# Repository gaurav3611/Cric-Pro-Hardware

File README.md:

# SSwinGG bat sensor: hardware and firmware, step by step

A small sensor that sits on a cricket bat and sends every movement of the bat to the SSwinGG dashboard over Bluetooth. This folder holds the circuit, the firmware, and a guide that builds it one stage at a time, so that each stage is tested before the next part is added.

It is written for someone who has not done this before. Each stage says what to wire, what to upload, what you should see, and what is going on between the parts.

## What has been checked, and what has not

- **Checked:** every sketch compiles for the ESP32-C3 Super Mini, with no warnings. Stages 1 to 8 have also been run on a computer against a pretend sensor, battery and dashboard, and what they print, send and do with the light was checked there. The 14-byte Bluetooth packet was read back with the web app's own code.
- **Not checked:** nothing here has run on real hardware yet. The pin orders in the drawings come from published pinouts, not from your boards, the battery circuit has not been built, and the printed circuit board has not been made.

So follow the stages in order, and trust the labels printed on your own boards over any drawing.

## Versions

**0.2.0, 2026-10-21.** C2, a 220 µF capacitor that steadies the 5V line, added to both zero PCB layouts and the full circuit. A proposed impact sensor: [a piezo disc wired without diodes](diagrams/impact-piezo.svg), not yet read by the firmware. The continuity tester also runs on an ESP32 DevKit. The phone app moved to [mobile_app_swing](https://github.com/gaurav3611/mobile_app_swing).

**0.1.0, 2026-10-17.** First version: the circuit, nine stages, the guides as PDF, the one-file firmware and the layout without the diode.

## Parts

| Part | Notes |
|---|---|
| ESP32-C3 Super Mini | The small board with a USB-C socket and eight pins on each side. |
| GY-BMI160 | The motion sensor board: acceleration and rotation on three axes each. |
| LiPo cell, 3.7 V, 1500 mAh | One cell with two leads. Buy one with a built-in protection board, which is the usual kind. |
| TP4056 charger module **with protection** | The version with six pads: `IN+ IN- B+ B- OUT+ OUT-`. See [the question about the charger](#is-the-tp4056-the-right-charger). |
| Slide switch | Three pins in a row, 2.54 mm apart, for example the SS12D00. |
| Diode 1N5817 | A Schottky diode. A 1N5819 also works and loses a little more voltage. |
| Zero PCB | At least 20 by 16 holes. The common 5 by 7 cm board is big enough. |
| Female header strips | Two with 8 pins, one with 7. With them the two boards can be unplugged. |
| Insulated hook-up wire | Thin single-strand wire. |
| USB-C cable that carries data | Charge-only cables give no serial port. |
| Phone charger, 5 V and 1 A or more | To charge the cell through the TP4056. |
| Only for stage 7 | Two 100 kilohm resistors and one 100 nanofarad ceramic capacitor. |

Tools: a soldering iron and solder, a multimeter, wire cutters, insulating tape or heat-shrink tube, and double-sided foam tape for mounting.

**[docs/parts-to-buy.pdf](docs/parts-to-buy.pdf) is the shopping list:** the exact name to search for, how many, and what to check before paying.

## Before you touch the battery

A LiPo cell stores a lot of energy and can catch fire when it is mistreated.

- **Never let the red and the black lead touch.** Cut and solder them one at a time, never both together.
- **Check which lead is plus with a multimeter** before soldering. Red is normally plus, but plugs are wired both ways.
- **Charge it only through the TP4056**, on a surface that cannot burn, and not unattended.
- **Do not use a cell that is swollen, dented or punctured.**
- **Protect it on the bat.** Mount it away from where the ball hits, with foam under it.

## The stages

Do them in order. Each folder under [stages/](stages/) holds one sketch and a page, `README.pdf`, with the steps. The links in the table open those pages.

| Stage | What you add | What you learn | It works when |
|---|---|---|---|
| [1. Blink](stages/01_blink/README.pdf) | The ESP32 board and a USB cable | Uploading, the Serial Monitor, outputs and inputs | The light blinks and lines appear |
| [2. I2C scan](stages/02_i2c_scan/README.pdf) | The sensor, on five wires | What I2C is, and addresses | It prints `RESULT: PASS` |
| [3. Read the sensor](stages/03_imu_read/README.pdf) | Nothing | Registers, bytes, counts and units | Four checks pass and z reads 1 g |
| [4. Swing speed](stages/04_swing_speed/README.pdf) | Nothing | Calibration, and the speed formula | A swing prints a speed |
| [5. Bluetooth](stages/05_ble_stream/README.pdf) | Nothing | Advertising, connecting, notifications, the packet | The test page shows 50 readings a second |
| [6. Battery](stages/06_battery_power/README.pdf) | Cell, charger, switch, diode | Where the power flows, charging, brownouts | It runs with no cable and counts no brownouts |
| [7. Battery level](stages/07_battery_level/README.pdf) | Optional: two resistors, one capacitor | Measuring a voltage | The printed voltage matches a multimeter |
| [8. The bat firmware](stages/08_sswingg_bat/README.pdf) | Nothing | How it all fits together | The dashboard records a shot |
| [9. WiFi](stages/09_wifi_to_api/README.pdf) | Optional: nothing | WiFi, HTTP and JSON | The API lists the bat as online |

Stages 1 to 5 run from the USB cable. The battery comes in at stage 6, when everything else is known to work.

## The whole circuit

| From | To | What it carries | Added in |
|---|---|---|---|
| `3V3` | `VIN` of the sensor | Power for the sensor, 3.3 volts | Stage 2 |
| `GND` | `GND` of the sensor | Ground | Stage 2 |
| `GPIO4` | `SCL` | I2C clock | Stage 2 |
| `GPIO3` | `SDA` | I2C data | Stage 2 |
| `SAO` of the sensor | `GND` | Fixes the sensor's address at 0x68 | Stage 2 |
| Cell, red lead | `B+` of the charger | Battery plus | Stage 6 |
| Cell, black lead | `B-` of the charger | Battery minus | Stage 6 |
| `OUT+` of the charger | Switch, an end pin | Battery plus, protected | Stage 6 |
| Switch, middle pin | Diode, plain end | Battery plus, switched | Stage 6 |
| Diode, striped end | `5V` | Power into the ESP32 board | Stage 6 |
| `OUT-` of the charger | `GND` | Ground | Stage 6 |
| Switch, middle pin | R1 | Battery plus, switched | Stage 7 |
| `GPIO0` | middle of R1 and R2 | Half the battery voltage. C1 goes from here to ground. | Stage 7 |
| R2, other end | `GND` | Ground | Stage 7 |

Leave the sensor's `3V3`, `CS`, `INT1`, `INT2` and `OCS` pins unconnected.

More drawings:

- [What each pin of the ESP32 is used for](diagrams/pin-map.svg)
- [The sensor on five wires](diagrams/stage-2-sensor-wiring.svg)
- [Where the power flows](diagrams/stage-6-power.svg)
- [Measuring the battery](diagrams/stage-7-battery-sense.svg)
- [Zero PCB layout, hole by hole](diagrams/zero-pcb-layout.svg), with the steps in [docs/build-on-zero-pcb.pdf](docs/build-on-zero-pcb.pdf)
- [The same layout without the diode](diagrams/zero-pcb-layout-no-diode.svg), with a wire in its place
- The printed circuit board, designed in KiCad: [the schematic](diagrams/pcb-schematic.svg), [the parts side](diagrams/pcb-top.svg) and [the solder side](diagrams/pcb-bottom.svg), with ordering and soldering steps in [docs/order-the-pcb.pdf](docs/order-the-pcb.pdf). No board has been made yet.

- [Impact sensor, a proposal](diagrams/impact-piezo.svg): a piezo disc on the blade, wired without diodes. The firmware does not read it yet.

## Is the TP4056 the right charger?

Yes. The chip is called TP4056. There is no common charger called TP4050, so that is almost certainly the module you have.

- **What it does.** It charges one LiPo cell from 5 volts. It holds the current steady until the cell reaches 4.2 volts, then holds 4.2 volts until the current has dropped to a tenth, and then stops.
- **Get the version with protection.** It has six pads instead of four, and two extra small chips. They disconnect the cell when it is drained below about 2.4 volts, charged above about 4.3 volts, or shorted.
- **The charging current is 1 amp as sold.** That suits a 1500 mAh cell: cells are normally charged at up to their capacity per hour, which here is 1.5 amps. A full charge takes about two hours. To charge more gently, see [docs/make-changes.pdf](docs/make-changes.pdf).
- **The ESP32-C3 Super Mini has no charger of its own**, which is why this module is needed.
- **It is not a switch and not a regulator.** The slide switch turns the bat off. The regulator on the ESP32 board makes the 3.3 volts.

## Set up the Arduino IDE

1. **Install the Arduino IDE**, version 2, from arduino.cc.
2. **Add the ESP32 boards:** Tools > Board > Boards Manager, search for `esp32`, and install "esp32 by Espressif Systems". This kit was compiled with version 3.3.11.
3. **Choose the board:** Tools > Board > esp32 > **Nologo ESP32C3 Super Mini**.
4. **Choose the port:** Tools > Port, the one that appears when the board is plugged in. On a Mac its name starts with `/dev/cu.usbmodem`.
5. **Open a sketch** with File > Open and pick the `.ino` file inside a stage folder.
6. **Upload**, then open Tools > Serial Monitor and set it to **115200** baud.

No library has to be installed. Everything the sketches need is in their own folders.

If an upload cannot connect: hold the BOOT button, press and release RESET, release BOOT, and upload again. Press RESET once afterwards to start the sketch.

## How it works, and how to change it

- [docs/parts-to-buy.pdf](docs/parts-to-buy.pdf) is the shopping list.
- [docs/phone-app.pdf](docs/phone-app.pdf) explains the phone app.
- [docs/how-it-works.pdf](docs/how-it-works.pdf) explains the whole chain: what the sensor measures, the I2C conversation, the packet, Bluetooth, the arithmetic of the dashboard, and the power circuit.
- [docs/make-changes.pdf](docs/make-changes.pdf) says what else has to change when you change a pin, a part, the name, the rate or the battery.
- [docs/build-on-zero-pcb.pdf](docs/build-on-zero-pcb.pdf) is the soldering guide.
- [docs/order-the-pcb.pdf](docs/order-the-pcb.pdf) is the same build on a printed circuit board: how to order it and solder it.
- [docs/troubleshooting.pdf](docs/troubleshooting.pdf) lists what can go wrong, by what you see.

## What is in this folder

| Path | What it is |
|---|---|
| `stages/01_blink` to `stages/09_wifi_to_api` | One Arduino sketch per stage, each with its own page, `README.pdf`. |
| `stages/08_sswingg_bat/` | The firmware that stays on the bat. Its settings are in `config.h`. |
| `app/` | The same recorder as a web page. `recorder.js` holds its logic, which `tools/check.mjs` tests. |
| `sswingg_bat_one_file/` | The same firmware as one file, for opening or pasting into the Arduino IDE on its own. `tools/make_one_file.mjs` makes it from stage 8. |
| `stages/*/bmi160.h` | The sensor driver. The same file in three folders, because the Arduino IDE only compiles files inside a sketch's own folder. |
| `stages/*/swing_packet.h` | Builds the 14-byte packet. This is the agreement with the web app. |
| `stages/*/battery.h` | Battery voltage to percent. |
| `diagrams/` | Every drawing as SVG, and `make_diagrams.py`, which draws them. |
| `docs/` | The seven guides listed above, as PDF. |
| `pcb/` | The printed circuit board as a KiCad 10 project, `sswingg-bat.kicad_pro`, with its own library of the kit's parts. `sswingg-bat-gerbers.zip` is what you upload to a maker, `bom.csv` the parts list. |
| `tools/make_pcb_files.mjs` | Runs KiCad's checks on the board and makes the Gerber zip, the parts list and the board drawings from the KiCad design. Needs KiCad. |
| `diagrams/diagrams.pdf` | All drawings in one file, one per page, for printing. |
| `tools/ble_test.html` | A page that connects to the bat from a browser and shows what it sends. |
| `tools/check.mjs` | Checks the whole kit without hardware. |
| `tools/make_pdfs.mjs` | Makes the PDFs from their Markdown sources. Those sources are kept out of the repository. This README is the only Markdown document in it. |
| `tools/sim/` | The simulator that `check.mjs` uses to run the sketches on a computer. |

## Check the kit without hardware

After changing a sketch, a pin or a drawing, run:

```bash
node tools/check.mjs            # under a minute
node tools/check.mjs --board    # also compiles every sketch for the ESP32-C3, several minutes
```

It needs Node 22 or newer and a C++ compiler. It confirms that the copies of the shared files are identical, that every sketch, the drawings and this README use the same pins, that the packet is what the web app expects, and that every sketch behaves as its stage describes when run in the simulator. When KiCad is installed, it also runs KiCad's checks on the PCB and confirms that its schematic is the circuit of the drawings. It cannot check soldering, radio range or a real battery.

You can also run a single sketch in the simulator and watch what it prints:

```bash
tools/sim/run.sh stages/04_swing_speed "swing@3000:400:900:1,end@6000"
```

The words of the scenario are listed at the top of [tools/sim/sim_main.cpp](tools/sim/sim_main.cpp).

## The phone app

[mobile_app_swing](https://github.com/gaurav3611/mobile_app_swing) holds SSwinGG recorder, an Android app written in Flutter, in its own repository. It connects to the bat, records each shot between Start and Stop, guesses the type of shot, and saves every reading as a CSV file in a folder per type, named like `pull_shot/pull_shot_001.csv`. Its README says how to build and install it.

[app/](app/) is the same recorder as a web page for Chrome on Android, for phones where installing an app is not wanted. [docs/phone-app.pdf](docs/phone-app.pdf) explains it.

## Using it with the dashboard

1. Open the SSwinGG dashboard in Chrome or Edge and sign in. The web app is in the [Cric-Pro-FE](https://github.com/gaurav3611/Cric-Pro-FE) repository.
2. Switch the bat on and wait for the slow blink.
3. Press **Connect Sensor** and choose `SSwinGG-Bat`.
4. Press **START SHOT**, swing, then press **STOP & SAVE SHOT**. The dashboard reads the sensor only between those two presses.

Only one program can be connected to the bat at a time. Close the test page first.

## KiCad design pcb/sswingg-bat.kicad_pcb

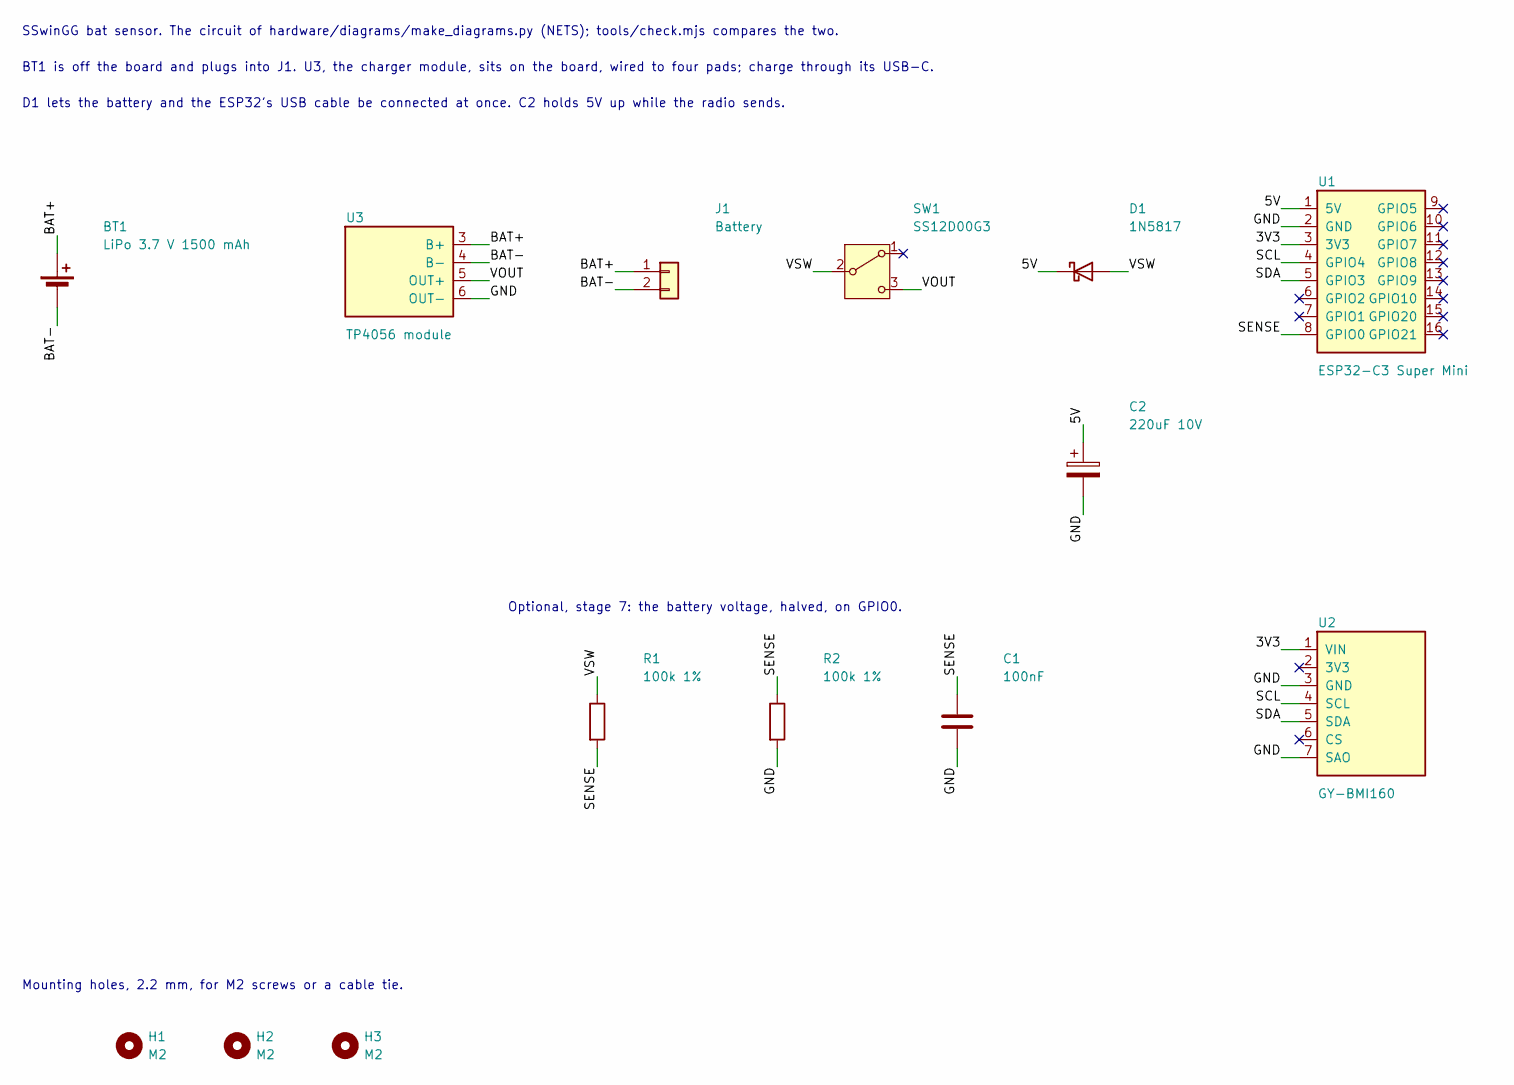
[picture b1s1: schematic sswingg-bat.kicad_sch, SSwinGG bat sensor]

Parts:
BT1: LiPo 3.7 V 1500 mAh
C1: 100nF; C_Disc_D5.0mm_W2.5mm_P5.00mm
C2: 220uF 10V; CP_Radial_D6.3mm_P2.50mm
D1: 1N5817; D_DO-41_SOD81_P10.16mm_Horizontal
H1, H2, H3: M2; MountingHole_2.2mm_M2
J1: Battery; JST_PH_B2B-PH-K_1x02_P2.00mm_Vertical
R1, R2: 100k 1%; R_Axial_DIN0207_L6.3mm_D2.5mm_P10.16mm_Horizontal
SW1: SS12D00G3; SW_Slide_SS12D00G3
U1: ESP32-C3 Super Mini; ESP32-C3_SuperMini_Socket
U2: GY-BMI160; GY-BMI160_Socket
U3: TP4056 module; TP4056_Module_Wired

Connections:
/3V3: U1.3 (3V3), U2.1 (VIN)
/5V: C2.1, D1.1 (K), U1.1 (5V)
/BAT+: BT1.1 (+), J1.1, U3.3 (B+)
/BAT-: BT1.2 (-), J1.2, U3.4 (B-)
/GND: C1.2, C2.2, R2.2, U1.2 (GND), U2.3 (GND), U2.7 (SAO), U3.6 (OUT-)
/SCL: U1.4 (GPIO4), U2.4 (SCL)
/SDA: U1.5 (GPIO3), U2.5 (SDA)
/SENSE: C1.1, R1.2, R2.1, U1.8 (GPIO0)
/VOUT: SW1.3 (C), U3.5 (OUT+)
/VSW: D1.2 (A), R1.1, SW1.2 (B)

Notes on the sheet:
SSwinGG bat sensor. The circuit of hardware/diagrams/make_diagrams.py (NETS); tools/check.mjs compares the two.
BT1 is off the board and plugs into J1. U3, the charger module, sits on the board, wired to four pads; charge through its USB-C.
D1 lets the battery and the ESP32's USB cable be connected at once. C2 holds 5V up while the radio sends.
Optional, stage 7: the battery voltage, halved, on GPIO0.
Mounting holes, 2.2 mm, for M2 screws or a cable tie.

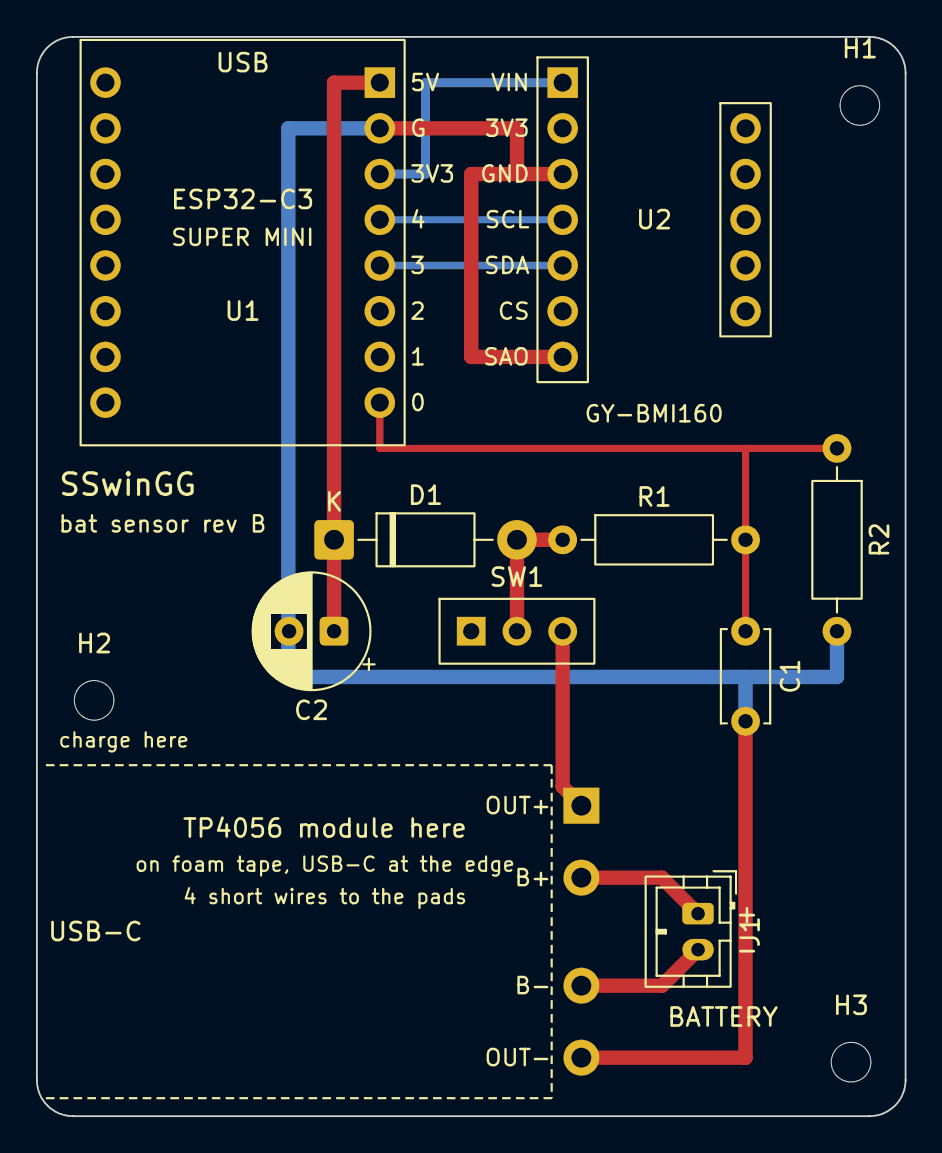
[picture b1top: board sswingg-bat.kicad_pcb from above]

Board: 2 copper layers, 48.3 x 60.0 mm, 13 parts (0 on the bottom side), 10 nets.

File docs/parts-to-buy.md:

# Parts to buy

Everything the bat sensor needs, with the name to search for in a shop and what to check before paying. The first table is the sensor itself. The second is only for the optional battery reading of stage 7.

## The sensor, stages 1 to 6 and 8

| # | Part | Name to search for | Qty | Check before buying |
|---|---|---|---|---|
| 1 | Microcontroller board | **ESP32-C3 Super Mini** development board | 1 | USB-C socket, eight pins on each long side, pins labelled `5V G 3.3 4 3 2 1 0` on one side. It comes with two loose 8-pin strips to solder on. |
| 2 | Motion sensor | **GY-BMI160** 6-axis module (Bosch BMI160) | 1 | "BMI160" in the name. An MPU6050 looks similar and does not work with this firmware. |
| 3 | Battery | **3.7 V 1500 mAh LiPo cell, size 803450**, with protection board | 1 | One cell, 3.7 V. About 8 by 34 by 50 mm. Two leads, red and black. Any plug is fine, it can be cut off. |
| 4 | Charger | **TP4056 charger module with protection**, 1 A, USB Type-C | 1 | Six pads: `IN+ IN- B+ B- OUT+ OUT-`. The version with only four pads has no protection: do not buy that one. |
| 5 | Power switch | **SS12D00G3** slide switch, SPDT, 3 pins | 1 | Pins 2.54 mm apart, so that it fits the zero PCB. Rated 0.5 A. |
| 6 | Diode | **1N5817** Schottky diode, 1 A, 20 V | 1 | The through-hole kind with two wire leads and a stripe at one end. A 1N5819 also works. |
| 7 | Board | **Zero PCB (perfboard), 5 by 7 cm**, holes 2.54 mm apart | 1 | At least 20 by 16 holes. Double-sided boards are easier to solder. |
| 8 | Sockets for the two boards | **Female header strip, single row, 2.54 mm** | two 8-pin, one 7-pin | A 40-pin strip can be cut instead. Each cut destroys one pin, so cut at the ninth and the eighth. |
| 9 | Wire | **Insulated hook-up wire**, 26 to 30 AWG, single strand | a few metres | Several colours help: red, black, and two others. |
| 10 | Cable to the computer | **USB-C cable that carries data** | 1 | Many cheap cables only charge. With those the board never shows up as a port. |
| 11 | Charger for the wall | **USB phone charger, 5 V, 1 A or more** | 1 | With a cable that fits the TP4056 module's socket. |
| 12 | Mounting | **Double-sided foam tape**, insulating tape or heat-shrink tube | a little | Foam under the board and the cell softens the knocks. |

It is worth buying two or three of items 5 and 6. They cost little and are easy to damage with a soldering iron.

## Only for the battery reading, stage 7

| # | Part | Name to search for | Qty | Check before buying |
|---|---|---|---|---|
| 13 | Two resistors | **100 kilohm resistor, 1/4 W, 1 %**, metal film | 2 | Both from the same strip, so they are as equal as possible. Colour bands: brown, black, black, orange, brown. |
| 14 | Capacitor | **100 nF ceramic capacitor, 50 V** | 1 | Also written 0.1 µF. Usually printed `104`. |

## Only if stage 6 reports brownouts

| # | Part | Name to search for | Qty | Check before buying |
|---|---|---|---|---|
| 15 | Capacitor | **220 µF electrolytic capacitor, 10 V or more** | 1 | It has a plus and a minus lead. The minus side is marked with a stripe. |

## Tools

| Tool | Notes |
|---|---|
| Soldering iron and solder | A fine tip, and thin solder with a flux core, 0.6 to 0.8 mm. |
| Multimeter | For continuity (the beep setting) and DC volts. It is not optional: the checks before first power need it. |
| Wire cutters and tweezers | |
| Computer with Chrome or Edge | For the Arduino IDE and for the Bluetooth test page. |

## Boards that look right and are not

- **ESP32-C3 Zero, ESP32-C3 DevKitM, LOLIN C3 Mini.** The firmware runs on them, because the chip is the same, but their pins sit in other places. The drawings and the zero PCB layout of this kit are for the Super Mini only.
- **Seeed XIAO ESP32-C3.** It has a charger built in, so the TP4056 part of this kit does not apply to it.
- **TP4056 module with four pads.** No protection for the cell.
- **Two cells, or a "7.4 V" pack.** The charger and the firmware are for one cell.
- **A 3.7 V cylindrical 18650 cell.** It works electrically, but it is heavy and hard to fix to a bat.

## Why these and not others

- **1500 mAh** runs the sensor for roughly a day of continuous use, and the cell is thin enough to tape flat to a bat. A 1000 mAh cell also works and is lighter.
- **The diode** is the cheapest way to make it safe to plug in the ESP32's USB cable while the battery is switched on. [stages/06_battery_power](../stages/06_battery_power/) explains it.
- **The switch goes in the plus wire**, after the charger. Then the cell can be charged with the bat switched off.
